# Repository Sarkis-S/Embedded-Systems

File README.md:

# PWM Fan Controller

Embedded systems project implementing multi-mode PWM-based fan speed control using Arduino, MOSFET switching, and motor load control.

This project documents the complete development flow from firmware logic and breadboard testing to hardware switching and signal validation.

⸻

## Project Goals

Build a fan controller capable of cycling through multiple speed modes using a single pushbutton.

Target behavior:

* Press 1 → Low speed
* Press 2 → Medium speed
* Press 3 → High speed
* Press 4 → Off

The project emphasizes both hardware and software reasoning.

⸻

## Core Concepts

This project focuses on:

* button input handling
* debounce logic
* edge detection
* state-machine design
* PWM generation
* MOSFET switching
* inductive load protection
* motor control
* signal verification

⸻

## Hardware Components

Controller

* Arduino Uno

Input

* Pushbutton

Output

* LED (Stage 2 validation)
* TT DC motor (final output)

Switching

* IRLZ44N

Protection

* 1N4007 flyback diode

Supporting Components

* 220Ω resistor
* 10kΩ resistor (original pull-down design)
* Jumper wires
* Breadboard

⸻

## Development Stages

⸻

Stage 1 — Button Input Validation

Goal:

* stable button input detection

Focus:

* INPUT_PULLUP configuration
* debounce handling
* edge detection

Key learning:

* pull-up vs pull-down behavior
* floating inputs
* mechanical switch bounce
* reliable press detection

Status: Complete

⸻

Stage 2 — PWM Output Validation

Goal:

* verify PWM control using LED brightness

Focus:

* multi-mode brightness control
* state transitions
* PWM mapping

Key learning:

* Arduino PWM range (0–255)
* duty cycle behavior
* state-driven output control

PWM Levels:

* Off → 0
* Low → 64
* Medium → 128
* High → 255

Status: Complete

⸻

Stage 3 — MOSFET Gate Control

Goal:

* control switching through MOSFET

Focus:

* gate control using PWM output
* switching behavior verification

Key learning:

* gate charge behavior
* MOSFET switching logic
* pull-down gate stability

Status: Pending

⸻

Stage 4 — Motor Integration

Goal:

* drive DC motor with PWM speed control

Focus:

* motor speed control
* full system integration

Key learning:

* motor response to PWM
* switching under load
* system-level validation

Status: Pending

⸻

Stage 5 — Signal Verification

Goal:

* inspect PWM waveform directly

Focus:

* logic analyzer validation
* duty cycle verification

Key learning:

* waveform interpretation
* duty cycle visualization
* software-to-signal correlation

Status: Pending

⸻

Firmware Highlights

Key firmware concepts used:

* debounced button input
* edge-triggered state changes
* multi-mode state machine
* array-based PWM lookup

Example PWM mapping:

int pwmLevels[] = {0, 64, 128, 255};

⸻

Tools

* Arduino IDE
* KiCad
* Logic Analyzer
* Git
* GitHub

⸻

Current Status

* Stage 1: Complete
* Stage 2: Complete
* Stage 3: In Progress
* Stage 4: Pending
* Stage 5: Pending

⸻

## Long-Term Objective

This project serves as a foundational embedded systems exercise for learning:

* hardware-software interaction
* real-world signal behavior
* actuator control
* embedded debugging methodology

It also serves as a stepping stone toward more advanced embedded systems development using Arduino, ESP32, and wireless communication systems.

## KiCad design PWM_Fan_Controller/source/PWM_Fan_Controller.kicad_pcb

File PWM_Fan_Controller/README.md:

# PWM Fan Controller

Embedded systems project implementing multi-mode PWM-based fan speed control using Arduino, MOSFET switching, and motor load control.

This project documents the complete development flow from firmware logic and breadboard testing to hardware switching and signal validation.

⸻

## Project Goals

Build a fan controller capable of cycling through multiple speed modes using a single pushbutton.

Target behavior:

* Press 1 → Low speed
* Press 2 → Medium speed
* Press 3 → High speed
* Press 4 → Off

The project emphasizes both hardware and software reasoning.

⸻

## Core Concepts

This project focuses on:

* button input handling
* debounce logic
* edge detection
* state-machine design
* PWM generation
* MOSFET switching
* inductive load protection
* motor control
* signal verification

⸻

## Hardware Components

Controller

* Arduino Uno

Input

* Pushbutton

Output

* LED (Stage 2 validation)
* TT DC motor (final output)

Switching

* IRLZ44N

Protection

* 1N4007 flyback diode

Supporting Components

* 220Ω resistor
* 10kΩ resistor (original pull-down design)
* Jumper wires
* Breadboard

⸻

## Development Stages

⸻

Stage 1 — Button Input Validation

Goal:

* stable button input detection

Focus:

* INPUT_PULLUP configuration
* debounce handling
* edge detection

Key learning:

* pull-up vs pull-down behavior
* floating inputs
* mechanical switch bounce
* reliable press detection

Status: Complete

⸻

Stage 2 — PWM Output Validation

Goal:

* verify PWM control using LED brightness

Focus:

* multi-mode brightness control
* state transitions
* PWM mapping

Key learning:

* Arduino PWM range (0–255)
* duty cycle behavior
* state-driven output control

PWM Levels:

* Off → 0
* Low → 64
* Medium → 128
* High → 255

Status: Complete

⸻

Stage 3 — MOSFET Gate Control

Goal:

* control switching through MOSFET

Focus:

* gate control using PWM output
* switching behavior verification

Key learning:

* gate charge behavior
* MOSFET switching logic
* pull-down gate stability

Status: Complete

⸻

Stage 4 — Motor Integration

Goal:

* drive DC motor with PWM speed control

Focus:

* motor speed control
* full system integration

Key learning:

* motor response to PWM
* switching under load
* system-level validation

Status: Complete

⸻

Stage 5 — Signal Verification

Goal:

* inspect PWM waveform directly

Focus:

* logic analyzer validation
* duty cycle verification

Key learning:

* waveform interpretation
* duty cycle visualization
* software-to-signal correlation

Status: Complete

⸻

Firmware Highlights

Key firmware concepts used:

* debounced button input
* edge-triggered state changes
* multi-mode state machine
* array-based PWM lookup

Example PWM mapping:

int pwmLevels[] = {0, 64, 128, 255};

⸻

Tools

* Arduino IDE
* KiCad
* Logic Analyzer
* Git
* GitHub

⸻

Current Status

* Stage 1: Complete
* Stage 2: Complete
* Stage 3: Complete
* Stage 4: Complete
* Stage 5: Complete

⸻

## Engineering Notes

This project taught me much more than just PWM motor control.

- A circuit can appear functional while still having wiring issues, poor design decisions, or hidden electrical problems. This project taught me to think beyond “it works.”
- As a visual learner, I initially focused too much on physical wire placement.
- Realizing components do not need direct visible lines to be connected and shared nets define electrical connectivity improved my KiCAD understanding and breadboard debugging.
- As wiring became more complex, I started understanding signal flow much better, which made debugging more logical and systematic.
- Seeing LOW, MEDIUM, and HIGH duty cycles side-by-side made PWM intuitive
- I finally understood that PWM is rapid ON/OFF switching, fixed frequencey and changing duty cycles.
⸻

## Long-Term Objective

This project serves as a foundational embedded systems exercise for learning:

* hardware-software interaction
* real-world signal behavior
* actuator control
* embedded debugging methodology

It also serves as a stepping stone toward more advanced embedded systems development using Arduino, ESP32, and wireless communication systems.

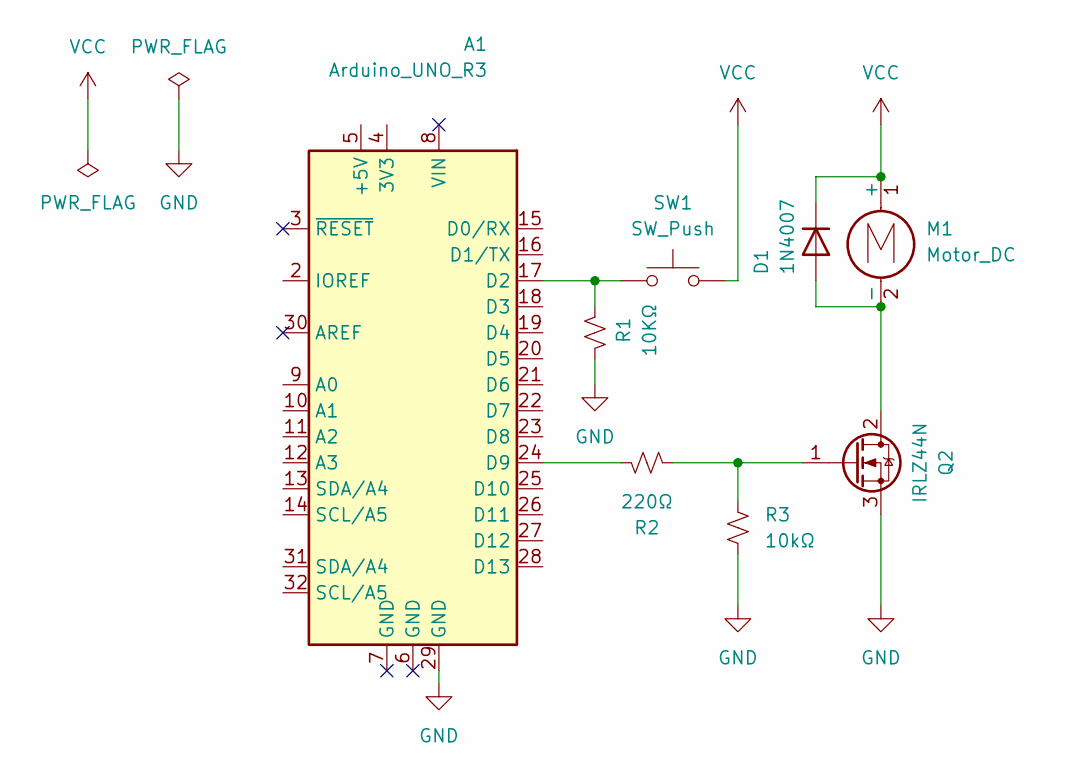
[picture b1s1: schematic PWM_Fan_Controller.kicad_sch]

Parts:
A1: Arduino_UNO_R3
D1: 1N4007; D_DO-41_SOD81_P10.16mm_Horizontal
M1: Motor_DC; PinHeader_1x02_P2.54mm_Vertical
Q2: IRLZ44N; TO-220-3_Vertical
R1: 10KΩ; R_Axial_DIN0207_L6.3mm_D2.5mm_P7.62mm_Horizontal
R2: 220Ω; R_Axial_DIN0207_L6.3mm_D2.5mm_P7.62mm_Horizontal
R3: 10kΩ; R_Axial_DIN0207_L6.3mm_D2.5mm_P7.62mm_Horizontal
SW1: SW_Push; SW_PUSH_6mm

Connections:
GND: A1.29 (GND), Q2.3 (S), R1.2, R3.2
unnamed: A1.17 (D2), R1.1, SW1.2
unnamed: A1.24 (D9), R2.1
unnamed: D1.2 (A), M1.2 (-), Q2.2 (D)
unnamed: Q2.1 (G), R2.2, R3.1
VCC: D1.1 (K), M1.1 (+), SW1.1

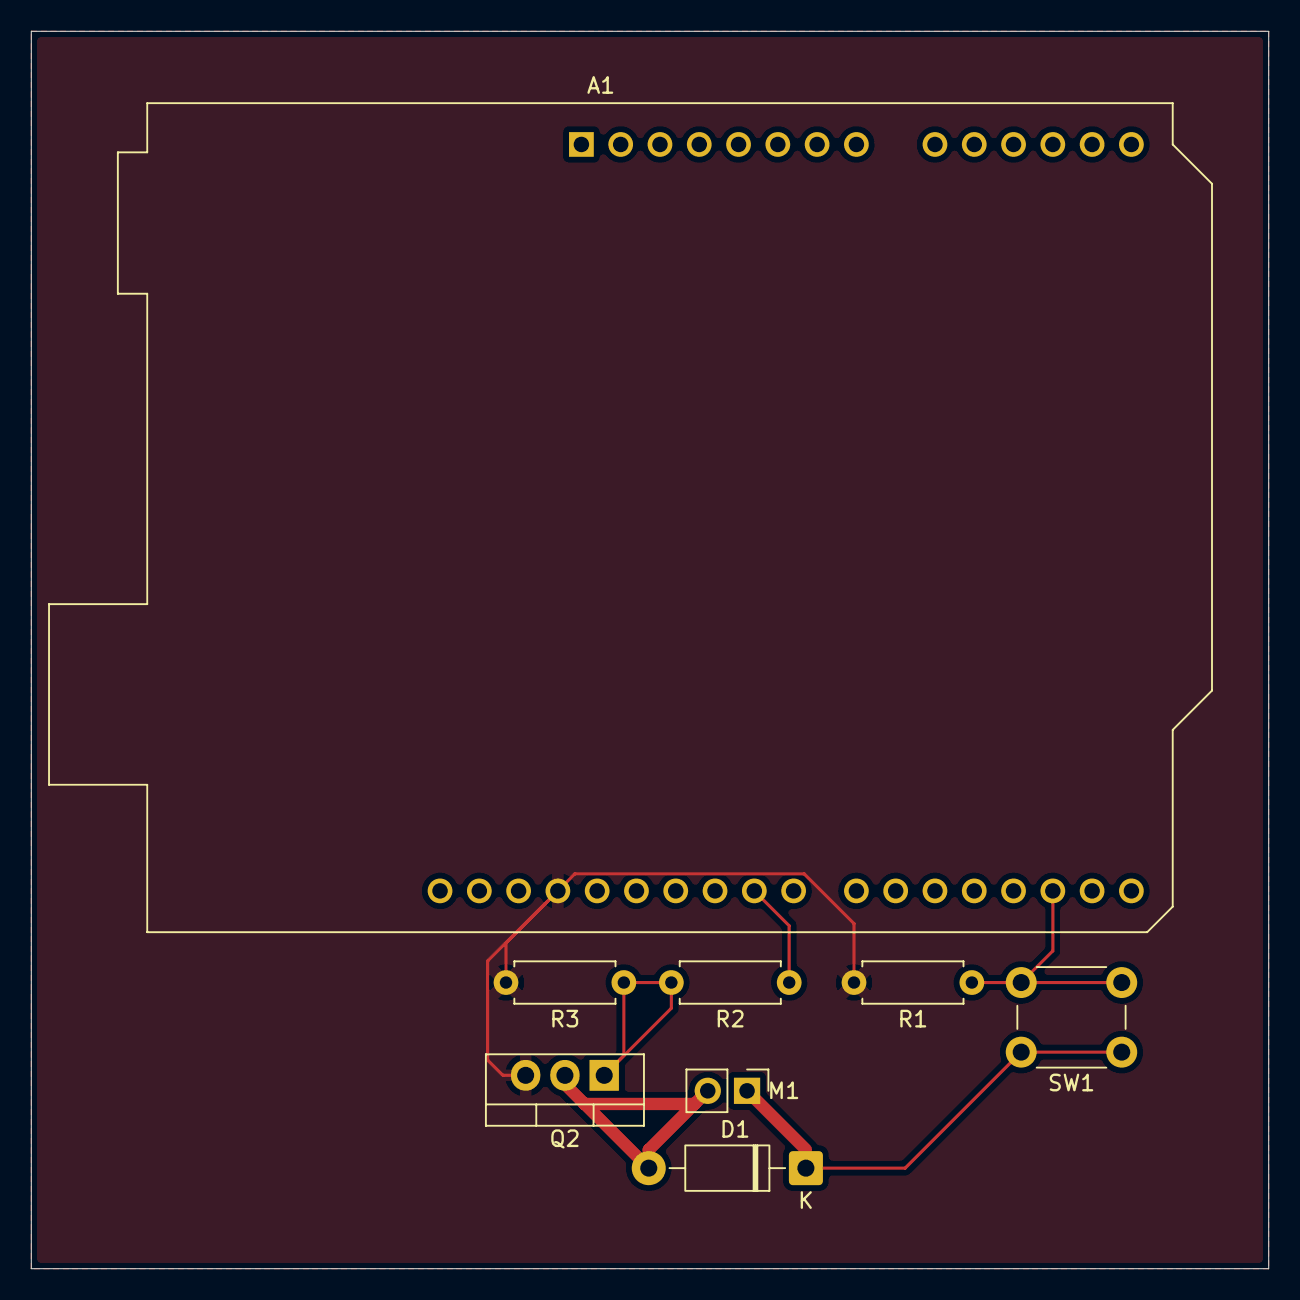
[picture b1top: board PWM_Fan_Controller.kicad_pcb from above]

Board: 2 copper layers, 80.0 x 80.0 mm, 8 parts (0 on the bottom side), 6 nets.

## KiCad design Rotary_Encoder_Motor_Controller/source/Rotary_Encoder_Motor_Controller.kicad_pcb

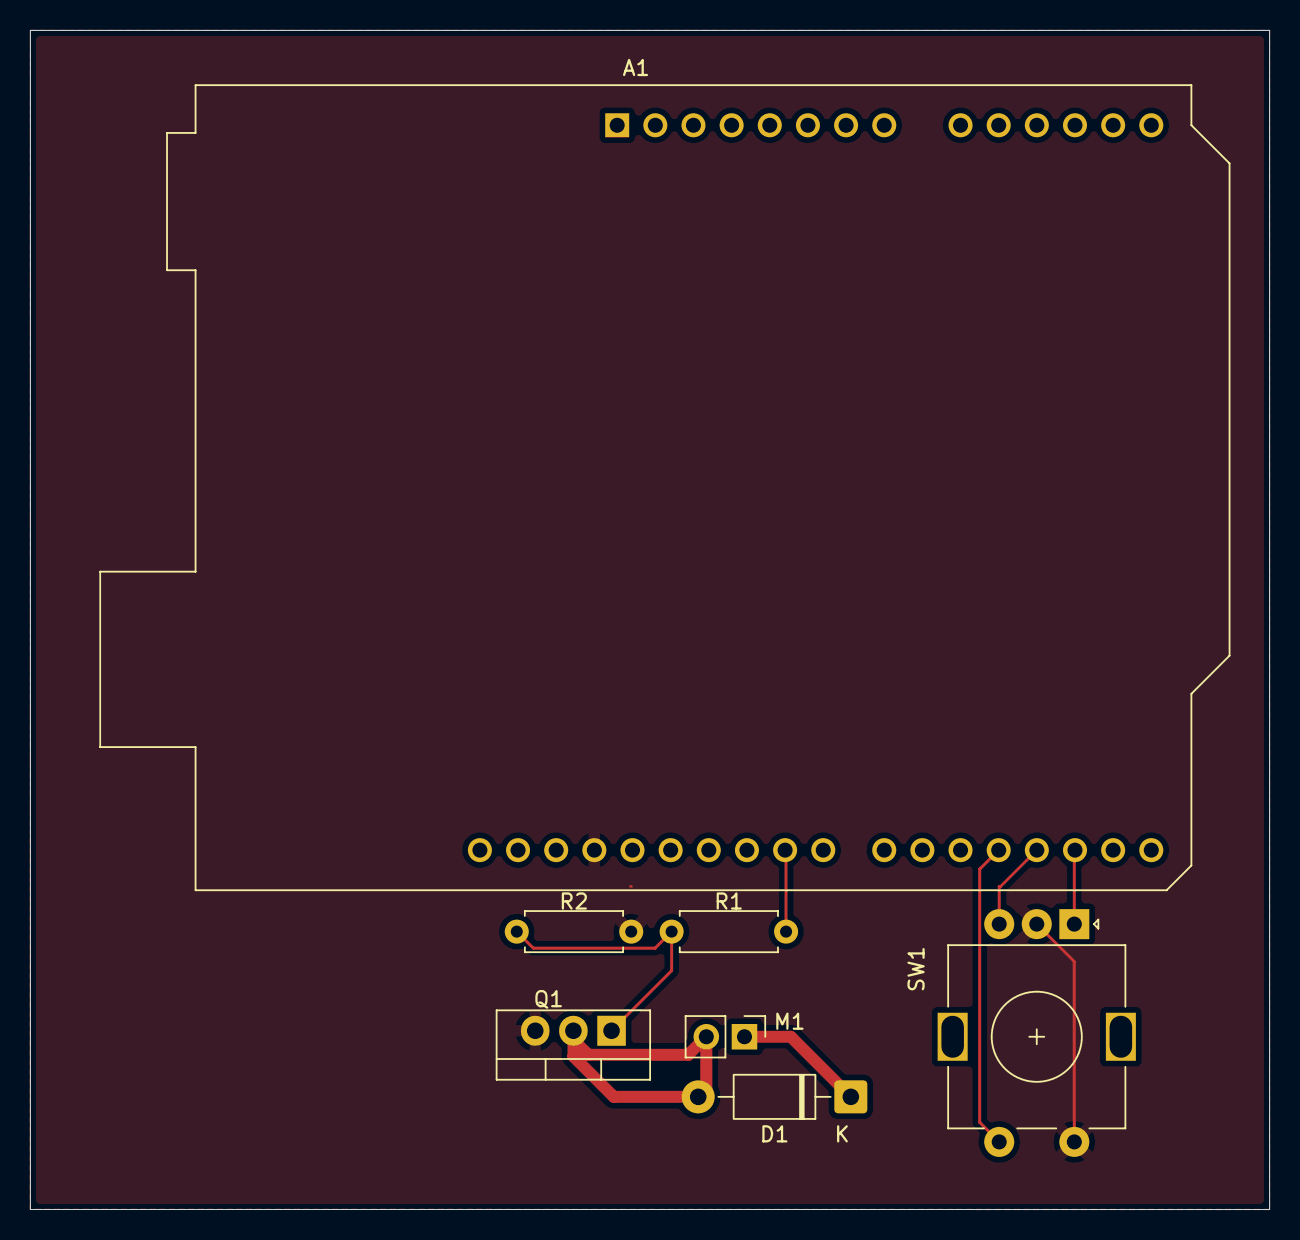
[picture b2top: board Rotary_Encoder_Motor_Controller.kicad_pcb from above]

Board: 2 copper layers, 82.5 x 78.5 mm, 7 parts (0 on the bottom side), 8 nets.

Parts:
A1: Arduino_UNO_R3
D1: D; D_DO-41_SOD81_P10.16mm_Horizontal
M1: Motor_DC; PinHeader_1x02_P2.54mm_Vertical
Q1: IRLZ44N; TO-220-3_Vertical
R1: 220Ω; R_Axial_DIN0207_L6.3mm_D2.5mm_P7.62mm_Horizontal
R2: 10KΩ; R_Axial_DIN0207_L6.3mm_D2.5mm_P7.62mm_Horizontal
SW1: RotaryEncoder_Switch_MP; RotaryEncoder_Alps_EC11E-Switch_Vertical_H20mm

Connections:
/ENC_A: A1.17 (D2), SW1.A
/ENC_B: A1.18 (D3), SW1.B
/ENC_SW: A1.19 (D4), SW1.S1
/PWM_OUT: A1.24 (D9), R1.1
GND: A1.29 (GND), Q1.3 (S), R2.2, SW1.C, SW1.S2
unnamed: D1.2 (A), M1.2 (-), Q1.2 (D)
unnamed: Q1.1 (G), R1.2, R2.1
VCC: D1.1 (K), M1.1 (+)

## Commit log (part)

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2026-06-30 Initialize Embedded Systems repository
2026-06-30 Initialize PWM Fan Controller with design files, README, and project structure
